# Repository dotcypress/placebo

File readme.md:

# Placebo

Truly minimal STM32G0/STM32C0 proto board.

## Features

* Breadboard/Perfboard friendly
* Power line bypass capacitors
* Reset circuit
* [`Tag-Connect TC2030-CTX-NL`](https://www.tag-connect.com/product/tc2030-ctx-nl-stdc14-for-use-with-stm32-processors-with-stlink-v3) programming connector
* Optional battery connector with LDO
* Optional configurable LED

## Pinout

## Rust firmware

1. Install rustup by following the instructions at https://rustup.rs
2. Install Cortex-M0, M0+, and M1 (ARMv6-M architecture) target: `rustup target add thumbv6m-none-eabi`
3. Install LLVM tools: `rustup component add llvm-tools-preview`
4. Install cargo-binutils: `cargo install cargo-binutils` (Note: on some Linux distros (e.g. Ubuntu) you may need to install the packages build-essential, gcc-arm-none-eabi, libssl-dev and pkg-config prior to installing cargo-binutils.)
5. Install cargo-generate: `cargo install cargo-generate`
6. Generate project: `cargo generate --git https://github.com/dotcypress/placebo-template.git`
7. Build firmware: `cargo build --release`
8. Flash microcontroller: `cargo run --release`

## Resources

- [Order PCB on Oshpark](https://oshpark.com/shared_projects/tT7z3ldx)
- [Schematics](docs/placebo.pdf)
- [Gerber files](docs/placebo.zip)
- [BOM](docs/placebo.csv)
- [Interactive BOM](https://htmlpreview.github.io/?https://github.com/dotcypress/placebo/blob/main/docs/ibom.html)

## License

Licensed under either of

- Apache License, Version 2.0 ([LICENSE-APACHE](LICENSE-APACHE) or
  http://www.apache.org/licenses/LICENSE-2.0)
- MIT license ([LICENSE-MIT](LICENSE-MIT) or http://opensource.org/licenses/MIT)

at your option.

### Contribution

Unless you explicitly state otherwise, any contribution intentionally submitted
for inclusion in the work by you, as defined in the Apache-2.0 license, shall be
dual licensed as above, without any additional terms or conditions.

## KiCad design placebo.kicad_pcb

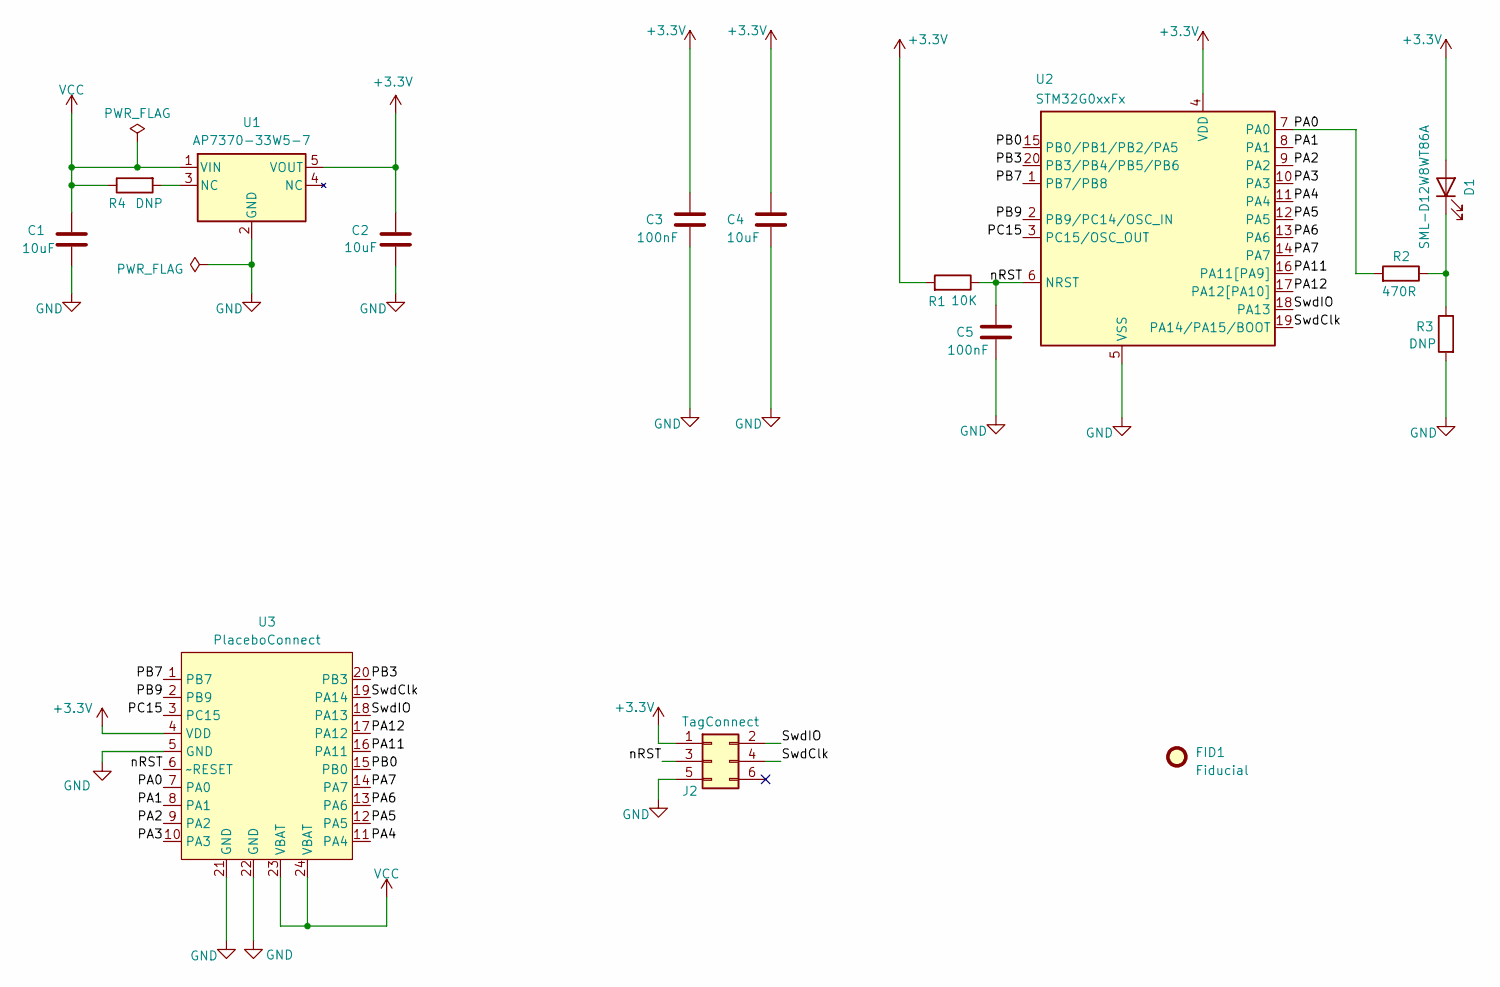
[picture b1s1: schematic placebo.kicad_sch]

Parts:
C1, C2, C4: 10uF; C_0603_1608Metric
C3, C5: 100nF; C_0603_1608Metric
D1: SML-D12W8WT86A; LED_0603_1608Metric
FID1: Fiducial; Fiducial_0.5mm_Mask1.5mm
J2: TagConnect; Tag-Connect_TC2030-IDC-NL_2x03_P1.27mm_Vertical
R1: 10K; R_0603_1608Metric
R2: 470R; R_0603_1608Metric
R3, R4: DNP; R_0603_1608Metric
U1: AP7370-33W5-7; TSOT-23-5_HandSoldering
U2: STM32G0xxFx; TSSOP-20_4.4x6.5mm_P0.65mm
U3: PlaceboConnect; PlaceboConnect_Cutout

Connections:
+3V3: C2.1, C3.1, C4.1, D1.2 (A), J2.1, R1.2, U1.5 (VOUT), U2.4 (VDD), U3.4 (VDD)
/PA0: R2.2, U2.7 (PA0), U3.7 (PA0)
/PA1: U2.8 (PA1), U3.8 (PA1)
/PA2: U2.9 (PA2), U3.9 (PA2)
/PA3: U2.10 (PA3), U3.10 (PA3)
/PA4: U2.11 (PA4), U3.11 (PA4)
/PA5: U2.12 (PA5), U3.12 (PA5)
/PA6: U2.13 (PA6), U3.13 (PA6)
/PA7: U2.14 (PA7), U3.14 (PA7)
/PA11: U2.16 (PA11[PA9]), U3.16 (PA11)
/PA12: U2.17 (PA12[PA10]), U3.17 (PA12)
/PB0: U2.15 (PB0/PB1/PB2/PA5), U3.15 (PB0)
/PB3: U2.20 (PB3/PB4/PB5/PB6), U3.20 (PB3)
/PB7: U2.1 (PB7/PB8), U3.1 (PB7)
/PB9: U2.2 (PB9/PC14/OSC_IN), U3.2 (PB9)
/PC15: U2.3 (PC15/OSC_OUT), U3.3 (PC15)
/SwdClk: J2.4, U2.19 (PA14/PA15/BOOT), U3.19 (PA14)
/SwdIO: J2.2, U2.18 (PA13), U3.18 (PA13)
/nRST: C5.1, J2.3, R1.1, U2.6 (NRST), U3.6 (~RESET)
GND: C1.2, C2.2, C3.2, C4.2, C5.2, J2.5, R3.2, U1.2 (GND), U2.5 (VSS), U3.5 (GND), U3.21 (GND), U3.22 (GND)
unnamed: D1.1 (K), R2.1, R3.1
unnamed: R4.2, U1.3 (NC)
VCC: C1.1, R4.1, U1.1 (VIN), U3.23 (VBAT), U3.24 (VBAT)

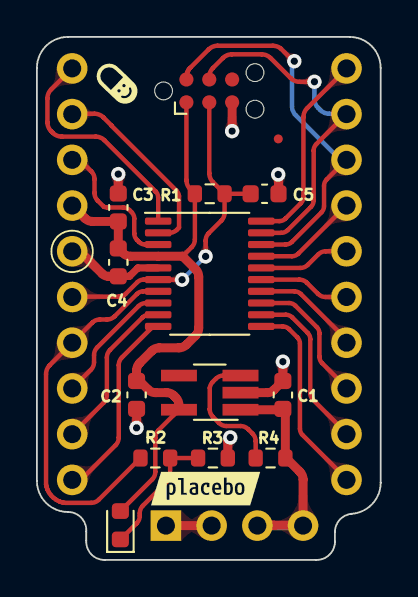
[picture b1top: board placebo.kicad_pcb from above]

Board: 2 copper layers, 19.1 x 29.1 mm, 17 parts (0 on the bottom side), 23 nets.

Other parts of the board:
LOGO1: LOGO
kibuzzard-631021FD: G***; kibuzzard-631021FD

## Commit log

2021-07-22 rev 1
2021-07-23 update docs
2021-07-23 fix typo
2021-07-24 update phato
2021-08-26 rev 2
2021-12-26 rev 0x3
2022-07-19 rev 0x4
2022-08-05 PlaceboConnect
2022-08-05 add pinout
2022-08-06 PlaceboConnect-cutout
2022-08-07 update pinout diagram
2022-08-14 rev. 0x6
2022-08-14 cleanup
2022-08-16 panel
2022-08-17 rev.0x6
2022-08-19 add cad files
2022-08-20 rev.0x7
2022-09-04 rev. 0x8
2022-09-17 panel rev. 0x8
2022-09-17 update BOM
2022-12-01 rev.0x9
2023-01-19 update photo
